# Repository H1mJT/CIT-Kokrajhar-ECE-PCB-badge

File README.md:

# CIT-Kokrajhar-ECE-PCB-badge

<table>
 <tr>
   <td> 
   <td>  
 </tr>
</table>

## A simple pcb which will light up the ECE text.

**Software: KiCAD 6.0.0**

**Badge Dimensions: 6.7cm×5cm**

**Design based on [CIT Kokrajhar logo](https://upload.wikimedia.org/wikipedia/en/e/ed/Central_Institute_of_Technology%2C_Kokrajhar_Logo.png)**

## Components Required:
* CR2032 battery holder SMD 20mm ([Example component](https://www.evelta.com/cr2032-battery-holder-cr2032-p28-24-1-smt/))- Qty:1
* SMD LED of any color with 0603 package ([Example Component](https://www.ktron.in/product/smd-blue-led-0603/))- Qty:13
* 3x6x2.5mm SMD slide Switch - Qty:1
* Brass Brooch Pin ([Example Component](https://www.beadsnfashion.com/product/brooch-pin-fittings-golden-0-75-inch))- Qty:1
* CR2032 Battery ([Example Component](https://www.hnhcart.com/products/cr2032-3v-225mah-lithium-coin-cell-battery))

## How to order the PCB

* Goto [JLCPCB](https://jlcpcb.com/) and upload the [Gerber Zip file](https://github.com/H1mJT/CIT-Kokrajhar-ECE-PCB-badge/tree/main/Gerber).

* PCB color: White

* Silkscreen color: Black

* Remove order number: Yes 
(Or there'll be a random number either on front or back ruining the badge aesthetics)

* Leave the rest as default.

## Ordering Components

Use any website to order the components like [Hnhcart](https://www.hnhcart.com/), [ktron](https://www.ktron.in/) etc
## Assembly

* Soldiering the battery holder and switch is fairly simple.

* Now let's come to LED's. 
Soldier the **LED's upside down**. The glowing side should be facing down since it'll shine throgh the transparent ECE text. Keep in mind the polarity of LED and follow the polarity as shown in silkscreen.

* Soldier the brooch pin at the top rectangle copper over the battery holder and you're done!!
*    

<br/><br/><br/><br/>

## Shitty Add-Ons  
So what's a shitty add on?  
It's a small PCB that connents to the main badge!! [Check this for more info](https://youtu.be/bXg2j4ttgis)  
There's slot for shitty add ons, so make any pcb design to add on it.  

<br/><br/><br/><br/>
<br/><br/><br/><br/><br/><br/><br/>

## Final Product

<table>
 <tr>
   <td> 
   <td> 
 </tr>
 <tr>
   <td> 
   <td> 
 </tr>
</table>

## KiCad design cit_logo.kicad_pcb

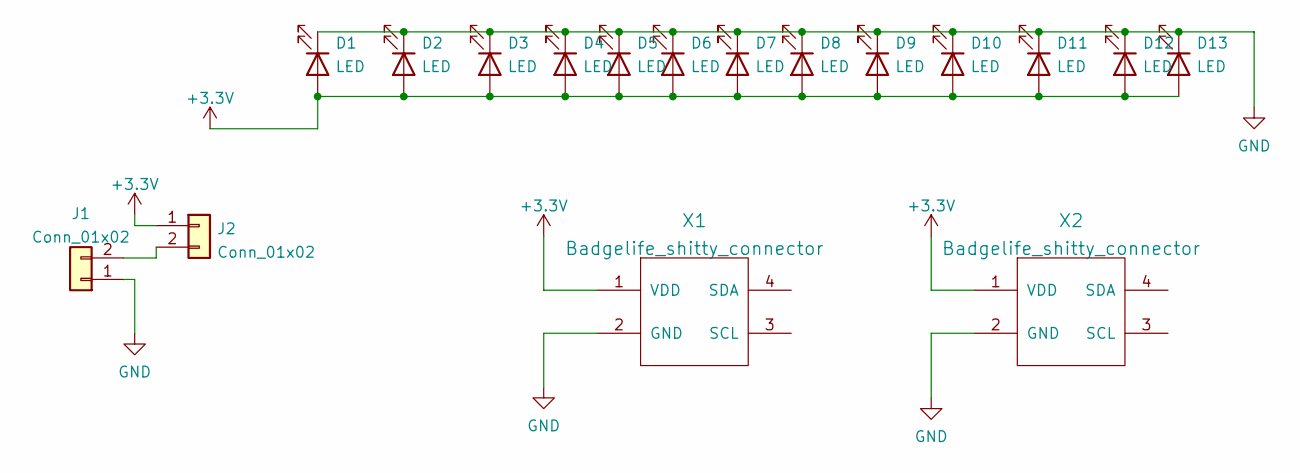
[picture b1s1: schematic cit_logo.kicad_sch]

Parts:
D1, D2, D3, D4, D5, D6, D7, D8, D9, D10, D11, D12, D13: LED; LED_0603_1608Metric_Pad1.05x0.95mm_HandSolder
J1: Conn_01x02; BatteryHolder_Keystone_3034_1x20mm
J2: Conn_01x02; SW_DIP_SPSTx01_Slide_6.7x4.1mm_W8.61mm_P2.54mm_LowProfile
X1, X2: Badgelife_shitty_connector; Badgelife-Shitty-2x2

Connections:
+3V3: D1.2 (A), D2.2 (A), D3.2 (A), D4.2 (A), D5.2 (A), D6.2 (A), D7.2 (A), D8.2 (A), D9.2 (A), D10.2 (A), D11.2 (A), D12.2 (A), D13.2 (A), J2.1, X1.1 (VDD), X2.1 (VDD)
GND: D1.1 (K), D2.1 (K), D3.1 (K), D4.1 (K), D5.1 (K), D6.1 (K), D7.1 (K), D8.1 (K), D9.1 (K), D10.1 (K), D11.1 (K), D12.1 (K), D13.1 (K), J1.1, X1.2 (GND), X2.2 (GND)
unnamed: J1.2, J2.2

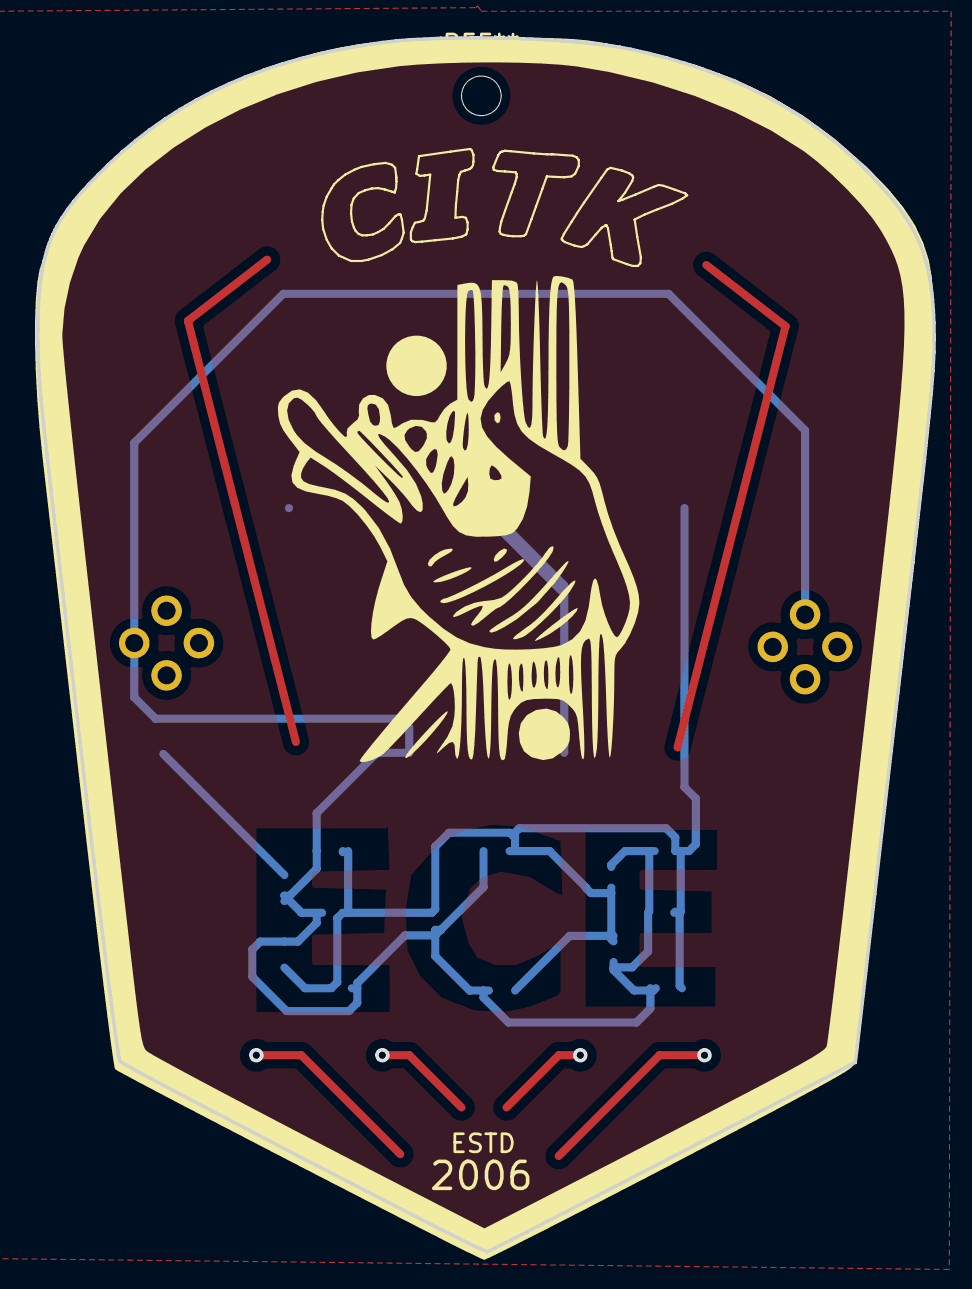
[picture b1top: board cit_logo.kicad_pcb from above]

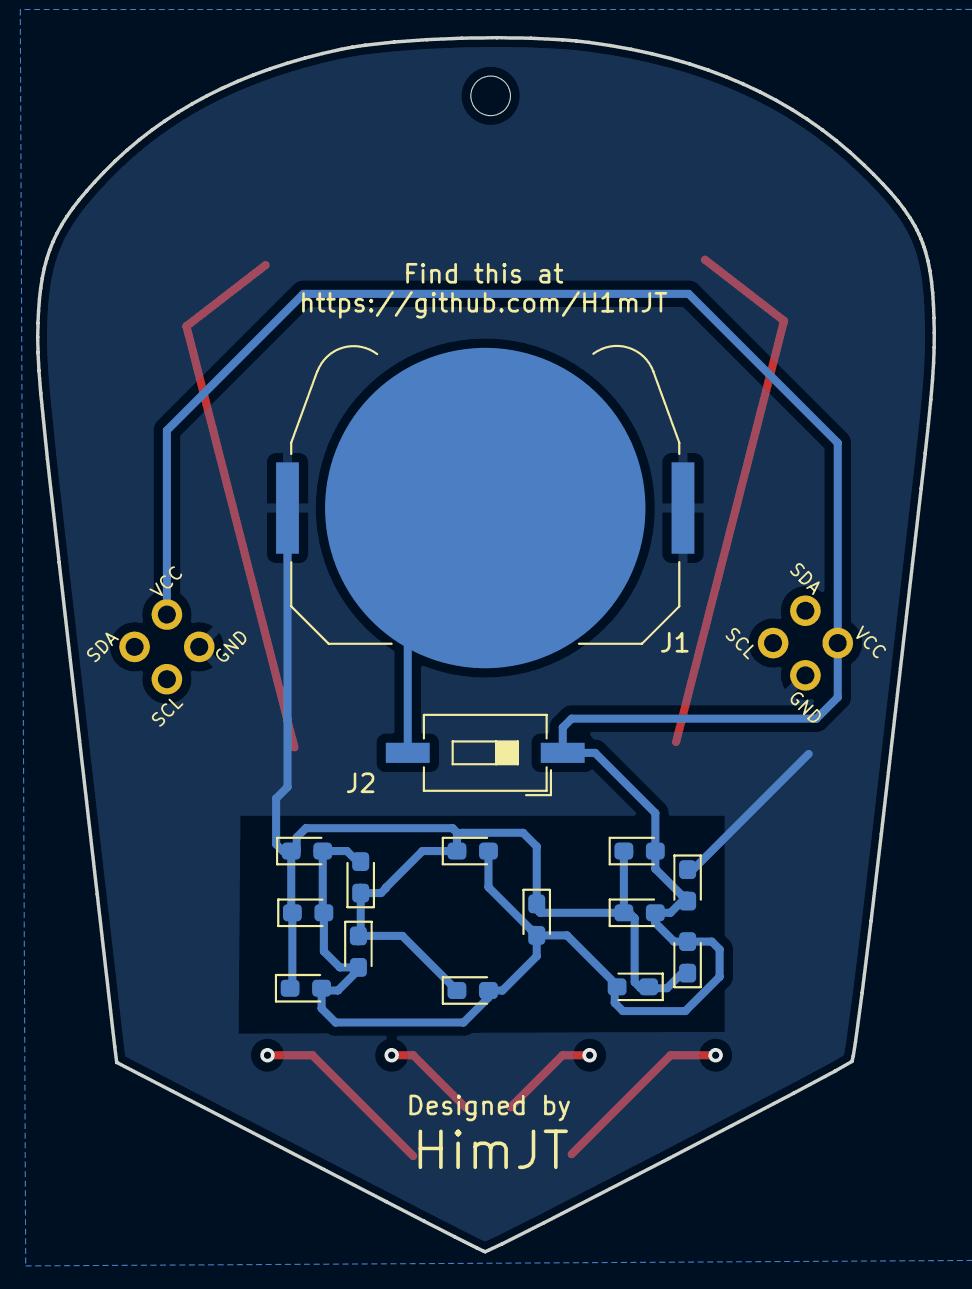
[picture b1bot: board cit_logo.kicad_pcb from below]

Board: 2 copper layers, 49.8 x 67.4 mm, 17 parts (15 on the bottom side), 3 nets.
